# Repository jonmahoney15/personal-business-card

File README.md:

# Personal Business Card

ESP32-C3 powered business card with a MAX7219 LED matrix displaying a Snake game.

## Firmware
The app is written in Rust. It makes use of `esp_hal` and the `MAX7219` crate.

The embassy framework is used as the runtime enabling async workflows.

## Hardware

| Component | Description |
|-----------|-------------|
| ESP32-C3 | Wi-Fi/BLE microcontroller running the firmware |
| MAX7219 | LED matrix driver IC |
| LED Matrix 8x8 | 64-LED display used for the Snake game |
| AMS1117 | 3.3V linear voltage regulator |
| USB-C | Power and programming interface |

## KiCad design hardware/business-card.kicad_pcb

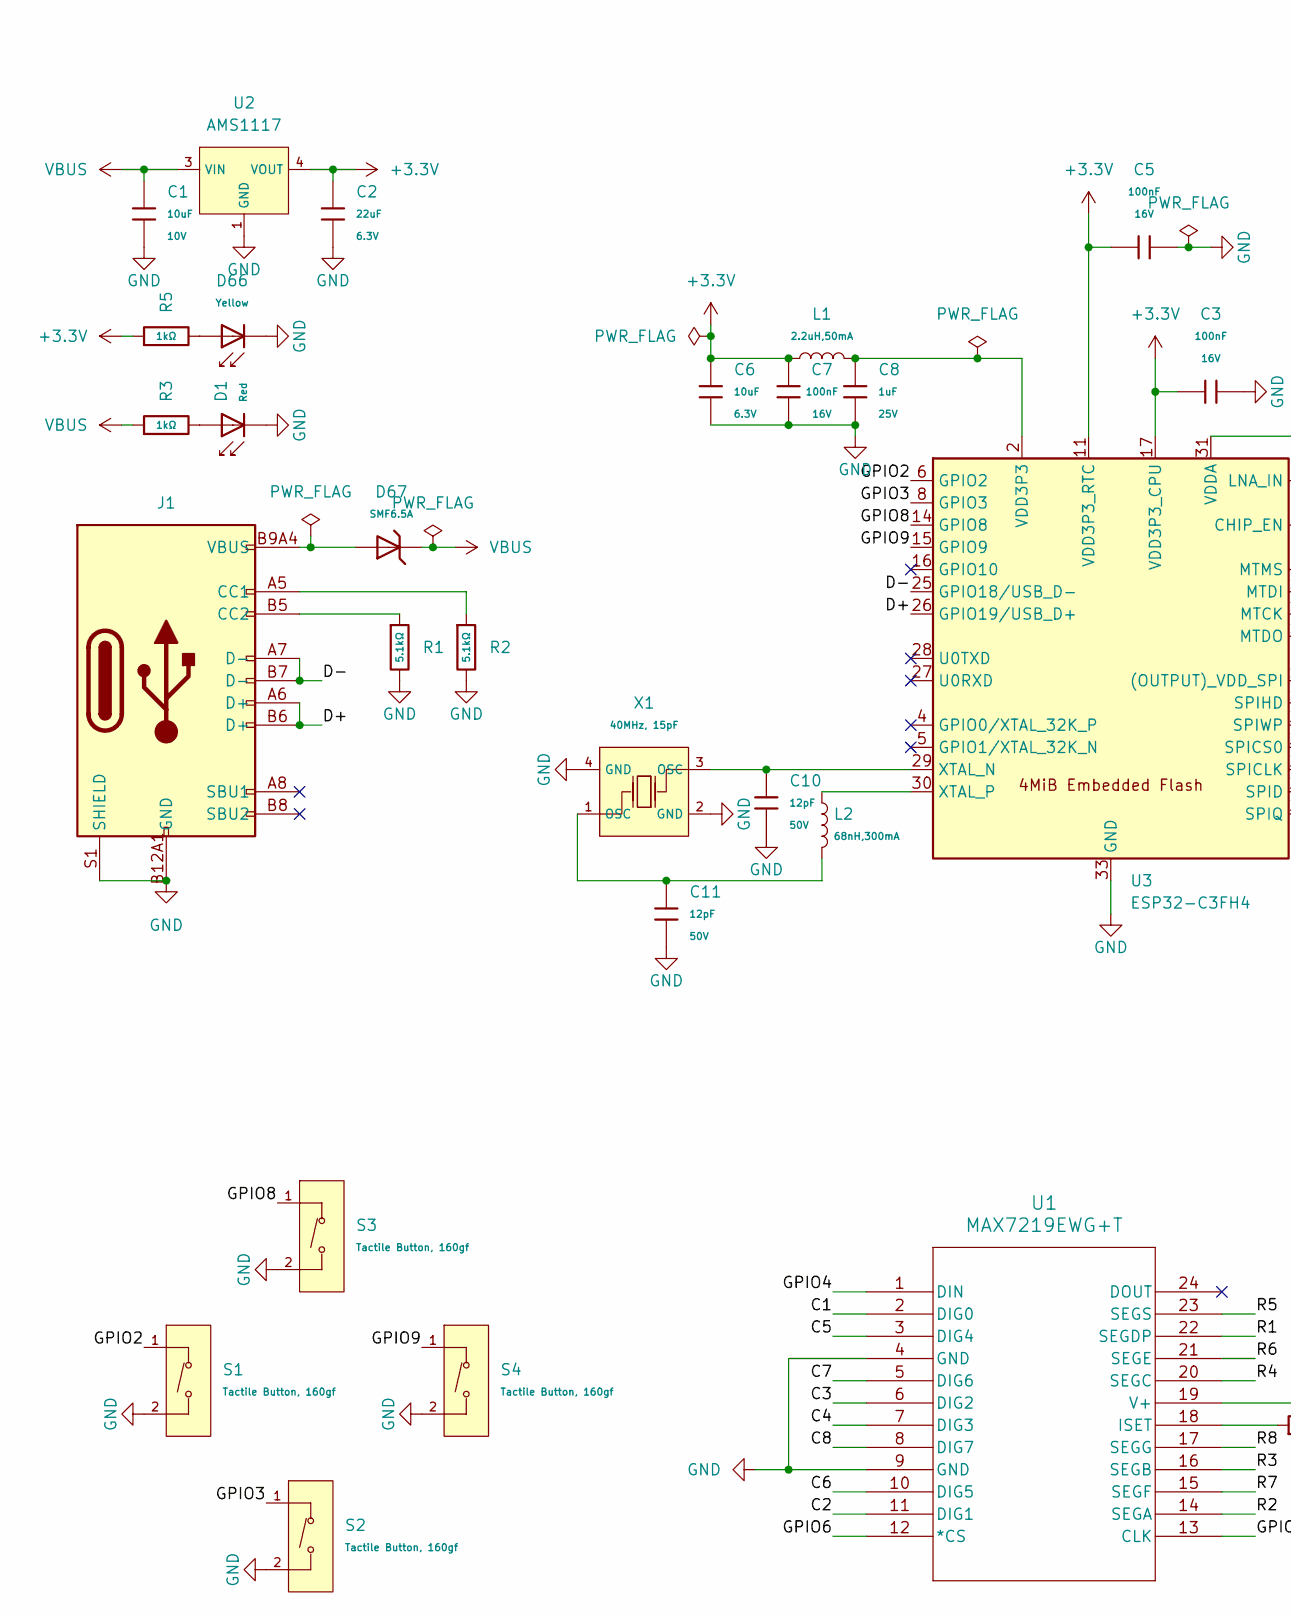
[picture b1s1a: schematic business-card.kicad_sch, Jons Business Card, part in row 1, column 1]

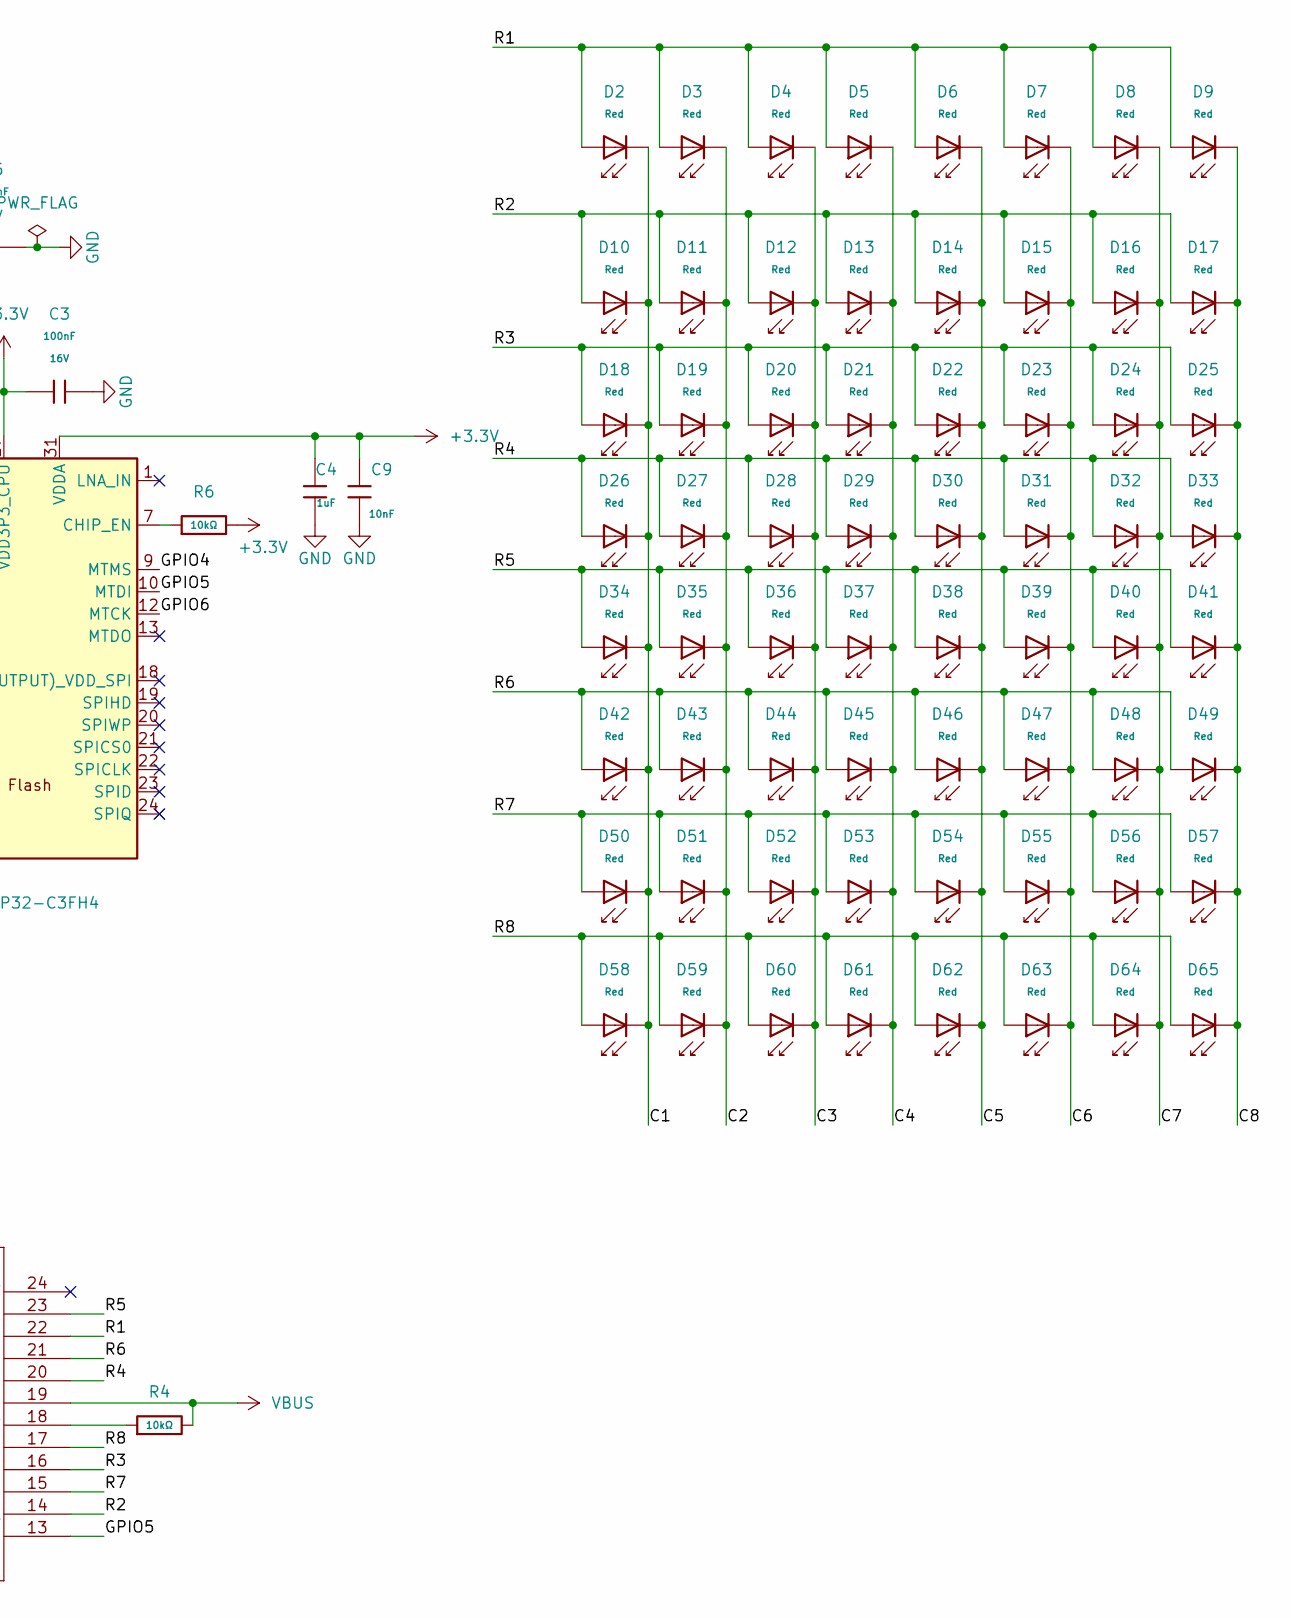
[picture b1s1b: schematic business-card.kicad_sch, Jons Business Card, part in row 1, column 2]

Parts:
C1: 10uF; C_0603; Voltage Rated 10V; Tolerance ±10%; Part CL10A106KP8NNNC; LCSC C19702
C2: 22uF; C_0603; Voltage Rated 6.3V; Tolerance ±20%; Part CL10A226MQ8NRNC; LCSC C59461
C3, C5, C7: 100nF; C_0402; Voltage Rated 16V; Tolerance ±10%; Part CL05B104KO5NNNC; LCSC C1525
C4, C8: 1uF; C_0402; Voltage Rated 25V; Tolerance ±10%; Part CL05A105KA5NQNC; LCSC C52923
C6: 10uF; C_0402; Voltage Rated 6.3V; Tolerance ±20%; Part CL05A106MQ5NUNC; LCSC C15525
C9: 10nF; C_0402; Voltage Rated 50V; Tolerance ±10%; Part CL05B103KB5NNNC; LCSC C15195
C10, C11: 12pF; C_0402; Voltage Rated 50V; Tolerance ±5%; Part 0402CG120J500NT; LCSC C1547
D1, D2, D3, D4, D5, D6, D7, D8, D9, D10, D11, D12, D13, D14, D15, D16, D17, D18, D19, D20, D21, D22, D23, D24, D25, D26, D27, D28, D29, D30, D31, D32, D33, D34, D35, D36, D37, D38, D39, D40, D41, D42, D43, D44, D45, D46, D47, D48, D49, D50, D51, D52, D53, D54, D55, D56, D57, D58, D59, D60, D61, D62, D63, D64, D65: Red; D_0603; Part KT-0603R; LCSC C2286
D66: Yellow; D_0603; Forward Voltage (VF) 1.6V~2.6V; Part NCD0603Y2; LCSC C89811
D67: SMF6.5A; D_SOD-123FL; Clamping Voltage 11.2V; Voltage - Breakdown 7.98V; Part SMF6.5A; LCSC C41376089
J1: Connector, USB-TYPE-C-16P; TYPE-C-SMD_HX-TYPE-C-16PIN; LCSC C2927039
L1: 2.2uH,50mA; L_0805; Tolerance ±10%; Part CMI201209U2R2KT; LCSC C1043
L2: 68nH,300mA; L_0603; Tolerance ±5%; Part SDCL1608C68NJTDF; LCSC C13415
R1, R2: 5.1kΩ; R_0402; Overload Voltage (Max) 50V; Tolerance ±1%; Part 0402WGF5101TCE; LCSC C25905
R3, R5: 1kΩ; R_0402; Overload Voltage (Max) 50V; Tolerance ±1%; Part 0402WGF1001TCE; LCSC C11702
R4, R6: 10kΩ; R_0402; Overload Voltage (Max) 50V; Tolerance ±1%; Part 0402WGF1002TCE; LCSC C25744
S1, S2, S3, S4: Tactile Button, 160gf; SW_TS-1088-AR02016; Voltage Rating (Dc) 12V; Part TS-1088-AR02016; LCSC C720477
U1: MAX7219EWG+T; 21-0042_W24&plus_1_MXM; LCSC C52476
U2: AMS1117; SOT-223-3_L6.5-W3.4-P2.30-LS7.0-BR; Output Voltage 3.3V; Dropout Voltage 1.3V@(800mA); Part AMS1117-3.3; LCSC C6186
U3: ESP32-C3FH4; QFN-32-1EP_5x5mm_P0.5mm_EP3.7x3.7mm_ThermalVias; LCSC C2858491
X1: 40MHz, 15pF; OSC-SMD_4P-L3.2-W2.5-BL_SIT8008BI; PartID X322540MPB4SI; LCSC C9010

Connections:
+3.3V: C2.1, C3.1, C4.1, C5.1, C6.1, C7.1, C9.1, L1.1, R5.1, R6.2, U2.2 (VOUT), U2.4 (VOUT), U3.11 (VDD3P3_RTC), U3.17 (VDD3P3_CPU), U3.31 (VDDA), U3.32 (VDDA)
/C1: D2.1, D10.1, D18.1, D26.1, D34.1, D42.1, D50.1, D58.1, U1.2 (DIG0)
/C2: D3.1, D11.1, D19.1, D27.1, D35.1, D43.1, D51.1, D59.1, U1.11 (DIG1)
/C3: D4.1, D12.1, D20.1, D28.1, D36.1, D44.1, D52.1, D60.1, U1.6 (DIG2)
/C4: D5.1, D13.1, D21.1, D29.1, D37.1, D45.1, D53.1, D61.1, U1.7 (DIG3)
/C5: D6.1, D14.1, D22.1, D30.1, D38.1, D46.1, D54.1, D62.1, U1.3 (DIG4)
/C6: D7.1, D15.1, D23.1, D31.1, D39.1, D47.1, D55.1, D63.1, U1.10 (DIG5)
/C7: D8.1, D16.1, D24.1, D32.1, D40.1, D48.1, D56.1, D64.1, U1.5 (DIG6)
/C8: D9.1, D17.1, D25.1, D33.1, D41.1, D49.1, D57.1, D65.1, U1.8 (DIG7)
/D+: J1.A6 (D+), J1.B6 (D+), U3.26 (GPIO19/USB_D+)
/D-: J1.A7 (D-), J1.B7 (D-), U3.25 (GPIO18/USB_D-)
/GPIO2: S1.1 (A), U3.6 (GPIO2)
/GPIO3: S2.1 (A), U3.8 (GPIO3)
/GPIO4: U1.1 (DIN), U3.9 (MTMS)
/GPIO5: U1.13 (CLK), U3.10 (MTDI)
/GPIO6: U1.12 (*CS), U3.12 (MTCK)
/GPIO8: S3.1 (A), U3.14 (GPIO8)
/GPIO9: S4.1 (A), U3.15 (GPIO9)
/R1: D2.2, D3.2, D4.2, D5.2, D6.2, D7.2, D8.2, D9.2, U1.22 (SEGDP)
/R2: D10.2, D11.2, D12.2, D13.2, D14.2, D15.2, D16.2, D17.2, U1.14 (SEGA)
/R3: D18.2, D19.2, D20.2, D21.2, D22.2, D23.2, D24.2, D25.2, U1.16 (SEGB)
/R4: D26.2, D27.2, D28.2, D29.2, D30.2, D31.2, D32.2, D33.2, U1.20 (SEGC)
/R5: D34.2, D35.2, D36.2, D37.2, D38.2, D39.2, D40.2, D41.2, U1.23 (SEGS)
/R6: D42.2, D43.2, D44.2, D45.2, D46.2, D47.2, D48.2, D49.2, U1.21 (SEGE)
/R7: D50.2, D51.2, D52.2, D53.2, D54.2, D55.2, D56.2, D57.2, U1.15 (SEGF)
/R8: D58.2, D59.2, D60.2, D61.2, D62.2, D63.2, D64.2, D65.2, U1.17 (SEGG)
GND: C1.2, C2.2, C3.2, C4.2, C5.2, C6.2, C7.2, C8.2, C9.2, C10.2, C11.2, D1.1, D66.1, J1.A12B1 (GND), J1.B12A1 (GND), J1.S1 (SHIELD), R1.2, R2.2, S1.2 (B), S2.2 (B), S3.2 (B), S4.2 (B), U1.4 (GND), U1.9 (GND), U2.1 (GND), U3.33 (GND), X1.2 (GND), X1.4 (GND)
unnamed: C8.1, L1.2, U3.2 (VDD3P3), U3.3 (VDD3P3)
unnamed: C11.1, L2.2, X1.1 (OSC)
unnamed: D1.2, R3.2
unnamed: D66.2, R5.2
unnamed: D67.2, J1.A9B4 (VBUS), J1.B9A4 (VBUS)
unnamed: J1.A5 (CC1), R2.1
unnamed: J1.B5 (CC2), R1.1
unnamed: R4.1, U1.18 (ISET)
unnamed: R6.1, U3.7 (CHIP_EN)
unnamed: C10.1, U3.29 (XTAL_N), X1.3 (OSC)
unnamed: L2.1, U3.30 (XTAL_P)
VBUS: C1.1, D67.1, R3.1, R4.2, U1.19 (V+), U2.3 (VIN)

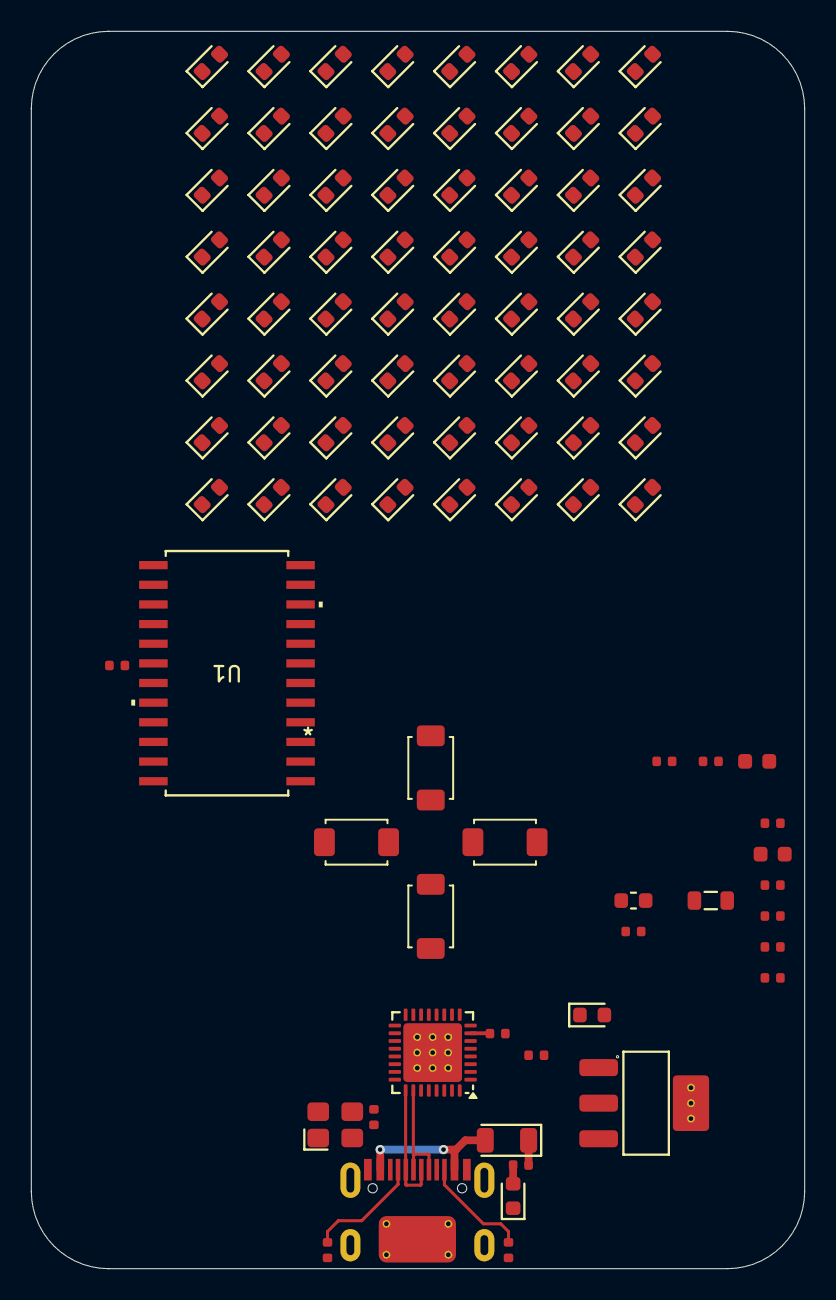
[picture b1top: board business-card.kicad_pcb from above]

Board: 2 copper layers, 50.0 x 80.0 mm, 95 parts (0 on the bottom side), 39 nets.

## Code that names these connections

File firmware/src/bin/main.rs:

#![no_std]
#![no_main]
#![deny(
    clippy::mem_forget,
    reason = "mem::forget is generally not safe to do with esp_hal types, especially those \
    holding buffers for the duration of a data transfer."
)]
#![deny(clippy::large_stack_frames)]

use embassy_executor::Spawner;
use embassy_time::{Duration, Timer};
use esp_hal::gpio::{Input, InputConfig, Level, Output, OutputConfig, Pull};
use esp_hal::spi::Mode;
use esp_hal::spi::master::{Config, Spi};
use esp_hal::time::Rate;
use esp_hal::timer::timg::TimerGroup;
use esp_hal::{clock::CpuClock, delay::Delay};
use log::{error, info};

#[path = "../max7219.rs"]
mod max7219;
use max7219::Max7219;

#[panic_handler]
fn panic(panic_info: &core::panic::PanicInfo) -> ! {
    error!("{}", panic_info);
    loop {}
}

esp_bootloader_esp_idf::esp_app_desc!();

#[allow(
    clippy::large_stack_frames,
    reason = "it's not unusual to allocate larger buffers etc. in main"
)]
#[esp_rtos::main]
async fn main(_spawner: Spawner) -> ! {
    esp_println::logger::init_logger_from_env();

    let config = esp_hal::Config::default().with_cpu_clock(CpuClock::max());
    let peripherals = esp_hal::init(config);

    let timg0 = TimerGroup::new(peripherals.TIMG0);
    let sw_interrupt =
        esp_hal::interrupt::software::SoftwareInterruptControl::new(peripherals.SW_INTERRUPT);
    esp_rtos::start(timg0.timer0, sw_interrupt.software_interrupt0);

    info!("Embassy initialized!");

    let mut delay = Delay::new();

    // SPI pins
    let sck = peripherals.GPIO5;
    let mosi = peripherals.GPIO4;
    let cs = Output::new(peripherals.GPIO6, Level::High, OutputConfig::default());

    let spi = Spi::new(
        peripherals.SPI2,
        Config::default()
            .with_frequency(Rate::from_mhz(1))
            .with_mode(Mode::_0),
    )
    .unwrap()
    .with_sck(sck)
    .with_mosi(mosi);

    let btn_up = Input::new(
        peripherals.GPIO8,
        InputConfig::default().with_pull(Pull::Up),
    );
    let btn_down = Input::new(
        peripherals.GPIO3,
        InputConfig::default().with_pull(Pull::Up),
    );
    let btn_left = Input::new(
        peripherals.GPIO2,
        InputConfig::default().with_pull(Pull::Up),
    );
    let btn_right = Input::new(
        peripherals.GPIO9,
        InputConfig::default().with_pull(Pull::Up),
    );

    let mut matrix = Max7219::new(spi, cs, &mut delay);
    matrix.clear();

    let mut row = 3;
    let mut col = 3;
    let mut dr = 0;
    let mut dc = 1;

    loop {
        if btn_up.is_low() {
            (dr, dc) = (-1, 0);
        }
        if btn_down.is_low() {
            (dr, dc) = (1, 0);
        }
        if btn_left.is_low() {
            (dr, dc) = (0, -1);
        }
        if btn_right.is_low() {
            (dr, dc) = (0, 1);
        }

        row = ((row as i8 + dr).rem_euclid(8)) as u8;
        col = ((col as i8 + dc).rem_euclid(8)) as u8;

        matrix.clear();
        matrix.set_pixel(row, col);

        Timer::after(Duration::from_millis(150)).await;
    }
}

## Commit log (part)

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2026-05-17 Initialization of PCB Business Card Repo
    This repo will hold both the software and hardware that makes up the
    business card. I will also try to outline the steps I took in creating
    it so others can have fun designing one like I did.
2026-05-23 Generated ESP firmware
    Using the esp-generate tool created the initial setup for the project.
    This will give the general ci and build tools needed to develop the
    firmware for the personal business card.
2026-05-23 Added PDF of schematic
    Provided a schematic pdf to easily view when looking through repo.
    Created using:
    ```
    $ kicad-cli sch export pdf business-card.kicad_sch
    ```
2026-05-24 Update wokwi diagram to look like pcb
    The primary change was adding all 4 buttons.
2026-05-25 Initial LED Movement
2026-06-27 Add hardware gitignore
    - added gitignore for kicad
    - reformatted the rust code
2026-06-27 Add Kicad project to hardware
    Updated the hardware directory to hold the entire kicad project. Now the
    pcb can be developed on multiple kicad instances and maintained in git.
2026-06-27 Updates to pcb working towards 0.2.0
